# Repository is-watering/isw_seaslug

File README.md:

# ISW-SEASLUG

ISW-SEASLUG is designed for use in combination with a trackball or joystick.

[Build guide](doc/buildguide.md)

## Dependencies (KiCad)
* [is-watering/isw-kbd-lib](https://github.com/is-watering/isw-kbd-lib)
* [Salicylic-acid3/KiCAD_FootPrint](https://github.com/Salicylic-acid3/KiCAD_FootPrint)
* [koktoh/BrownSugar_KBD_KiCad_Library](https://github.com/koktoh/BrownSugar_KBD_KiCad_Library)

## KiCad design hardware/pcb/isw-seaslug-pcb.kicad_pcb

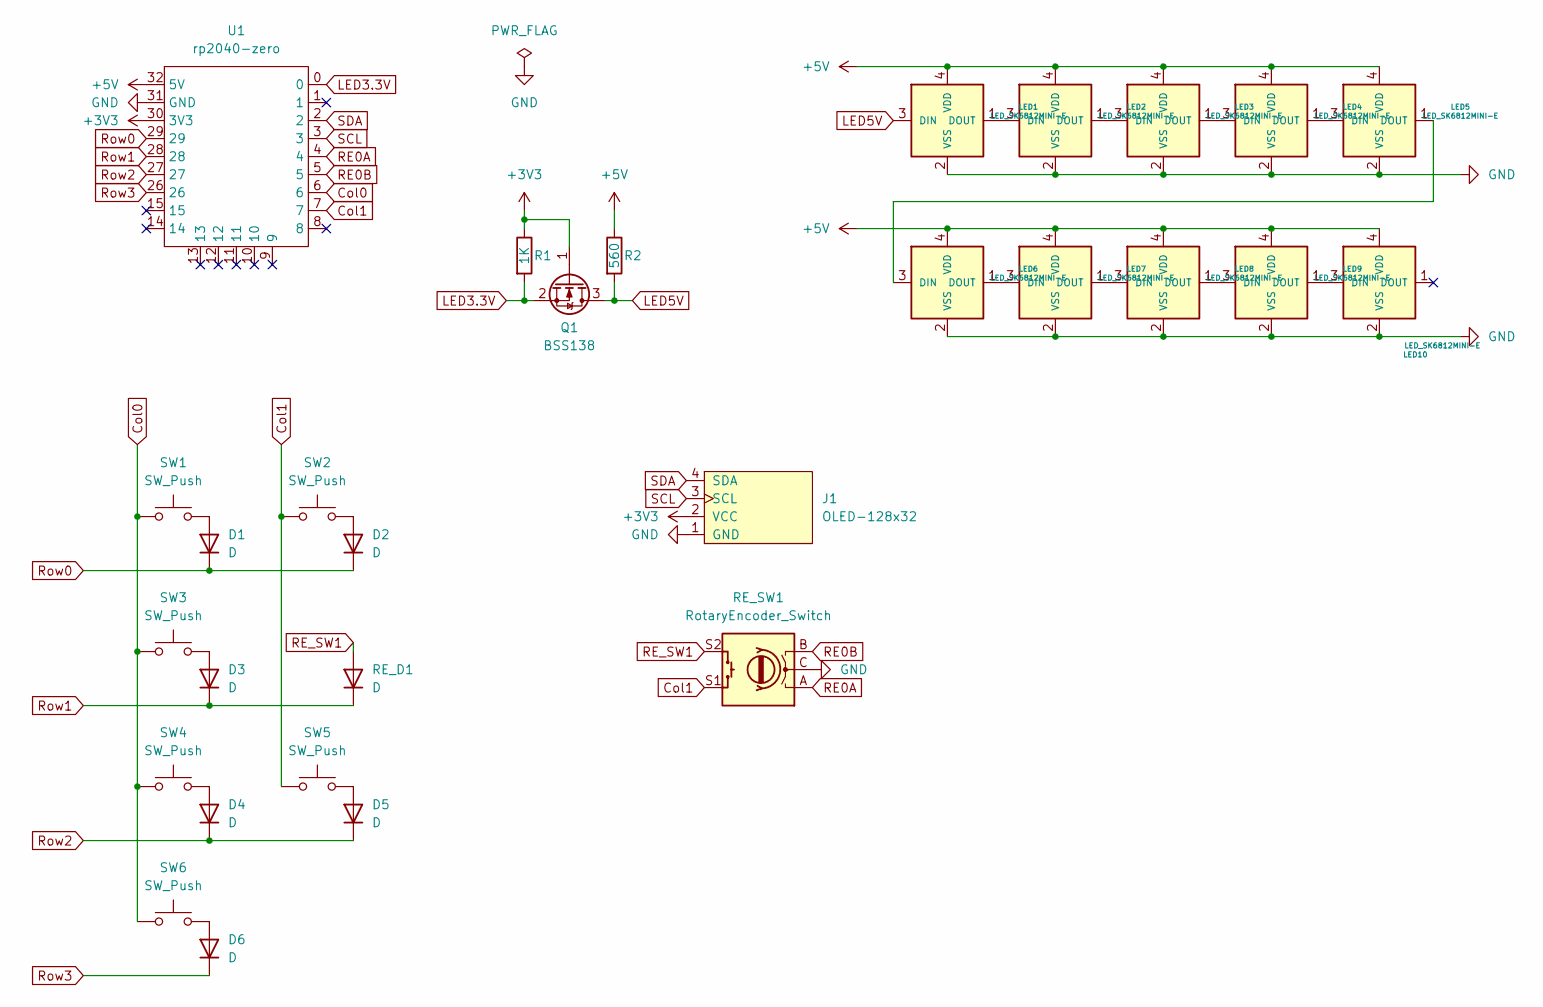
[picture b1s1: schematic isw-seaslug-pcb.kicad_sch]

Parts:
D1, D2, D3, D4, D5, D6: D; Diode_SMD
J1: OLED-128x32; StickPointV
LED1, LED2, LED3, LED4, LED5, LED6, LED7, LED8, LED9, LED10: LED_SK6812MINI-E; LED_SK6812MINI-E_UG
Q1: BSS138; SOT-23
R1, R2: R; R_Axial_DIN0207_L6.3mm_D2.5mm_P7.62mm_Horizontal
RE_D1: D; Diode_SMD
RE_SW1: RotaryEncoder_Switch; RotaryEncoder_EVQWGD001
SW1, SW2, SW3, SW4, SW5, SW6: SW_Push; CherryMX_Hotswap_1u
U1: rp2040-zero; RP2040-Zero-THT

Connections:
+3V3: J1.2 (VCC), Q1.1 (G), R1.1, U1.30 (3V3)
+5V: LED1.4 (VDD), LED2.4 (VDD), LED3.4 (VDD), LED4.4 (VDD), LED5.4 (VDD), LED6.4 (VDD), LED7.4 (VDD), LED8.4 (VDD), LED9.4 (VDD), LED10.4 (VDD), R2.1, U1.32 (5V)
Col0: SW1.1, SW3.1, SW4.1, SW6.1, U1.6
Col1: RE_SW1.S1, SW2.1, SW5.1, U1.7
GND: J1.1 (GND), LED1.2 (VSS), LED2.2 (VSS), LED3.2 (VSS), LED4.2 (VSS), LED5.2 (VSS), LED6.2 (VSS), LED7.2 (VSS), LED8.2 (VSS), LED9.2 (VSS), LED10.2 (VSS), RE_SW1.C, U1.31 (GND)
LED3.3V: Q1.2 (S), R1.2, U1.0
LED5V: LED1.3 (DIN), Q1.3 (D), R2.2
unnamed: D1.2 (A), SW1.2
unnamed: D2.2 (A), SW2.2
unnamed: D3.2 (A), SW3.2
unnamed: D4.2 (A), SW4.2
unnamed: D5.2 (A), SW5.2
unnamed: D6.2 (A), SW6.2
unnamed: LED1.1 (DOUT), LED2.3 (DIN)
unnamed: LED2.1 (DOUT), LED3.3 (DIN)
unnamed: LED3.1 (DOUT), LED4.3 (DIN)
unnamed: LED4.1 (DOUT), LED5.3 (DIN)
unnamed: LED5.1 (DOUT), LED6.3 (DIN)
unnamed: LED6.1 (DOUT), LED7.3 (DIN)
unnamed: LED7.1 (DOUT), LED8.3 (DIN)
unnamed: LED8.1 (DOUT), LED9.3 (DIN)
unnamed: LED9.1 (DOUT), LED10.3 (DIN)
RE0A: RE_SW1.A, U1.4
RE0B: RE_SW1.B, U1.5
RE_SW1: RE_D1.2 (A), RE_SW1.S2
Row0: D1.1 (K), D2.1 (K), U1.29
Row1: D3.1 (K), RE_D1.1 (K), U1.28
Row2: D4.1 (K), D5.1 (K), U1.27
Row3: D6.1 (K), U1.26
SCL: J1.3 (SCL), U1.3
SDA: J1.4 (SDA), U1.2

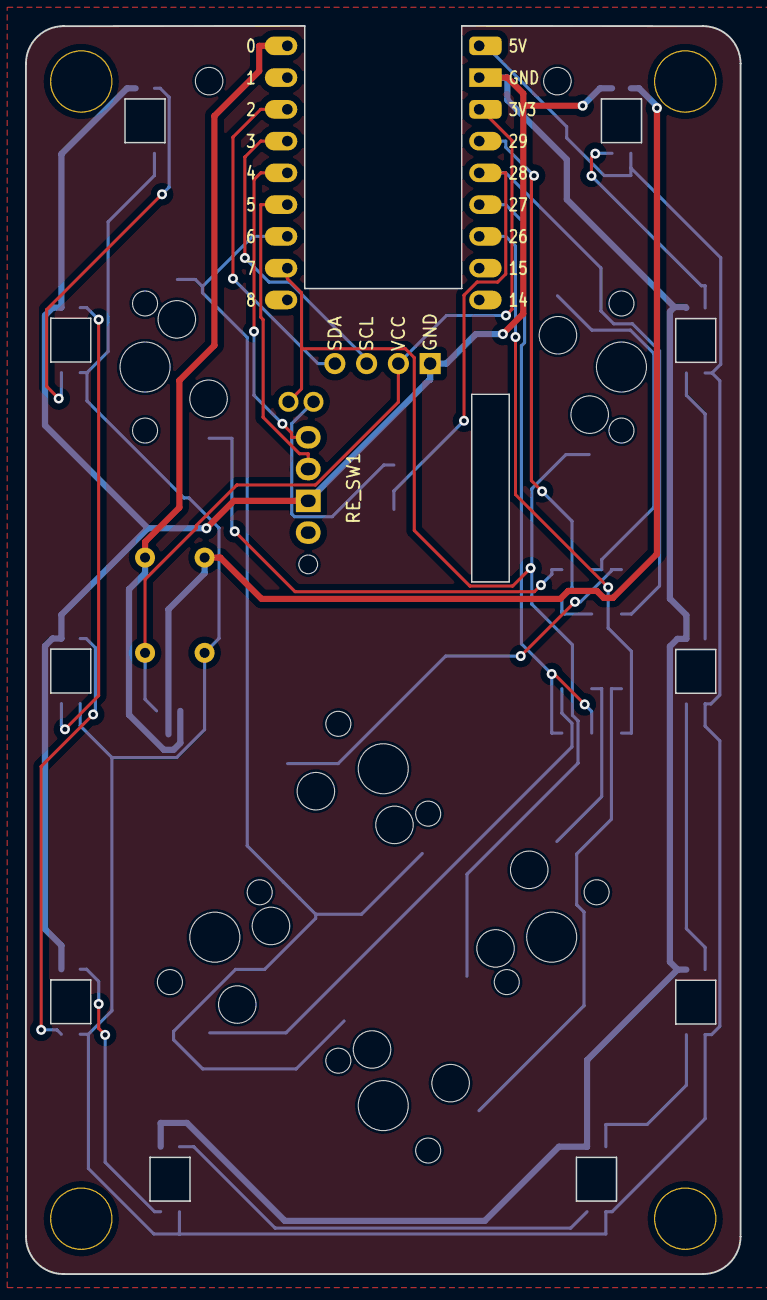
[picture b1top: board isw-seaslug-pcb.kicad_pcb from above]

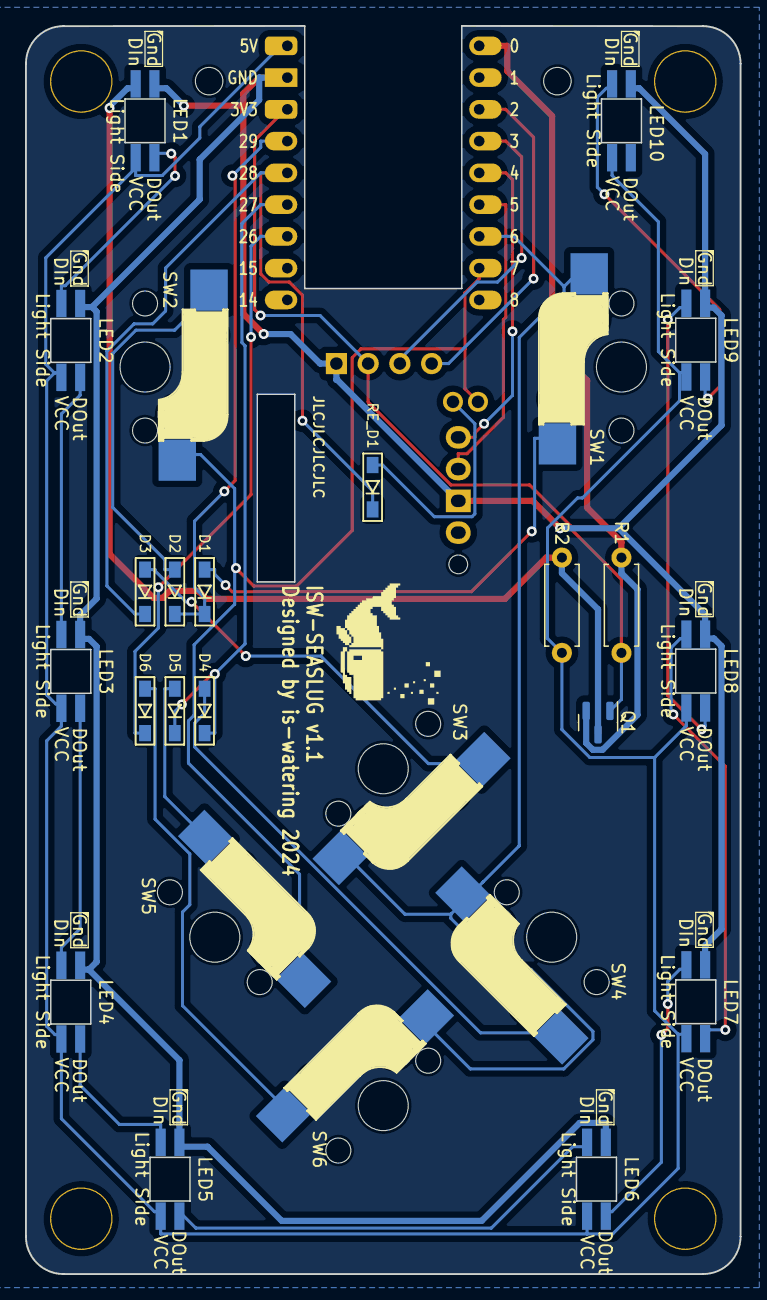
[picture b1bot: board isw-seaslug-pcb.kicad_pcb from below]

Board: 2 copper layers, 57.1 x 99.8 mm, 35 parts (4 on the bottom side), 31 nets.

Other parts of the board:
Ref01, Ref02, Ref03, Ref04: Val01; m2_Spacer_Hole
Ref11, Ref12: Val02; m2_Screw_Hole

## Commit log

2024-10-31 update: build guide
2024-10-31 add: img
